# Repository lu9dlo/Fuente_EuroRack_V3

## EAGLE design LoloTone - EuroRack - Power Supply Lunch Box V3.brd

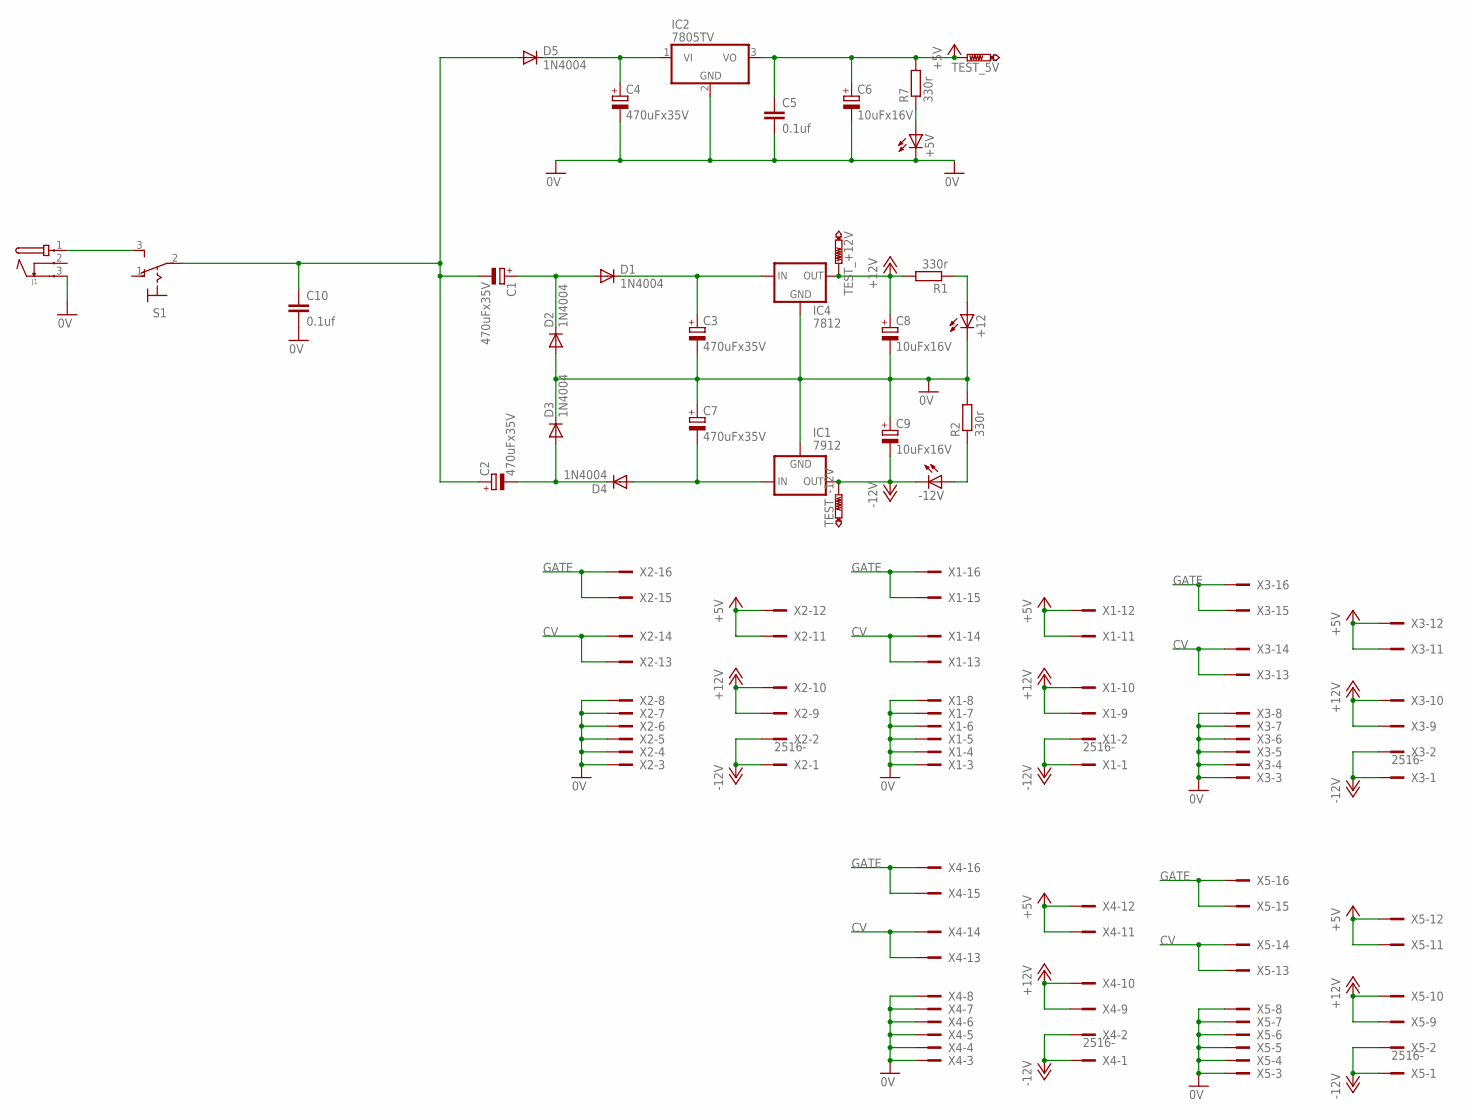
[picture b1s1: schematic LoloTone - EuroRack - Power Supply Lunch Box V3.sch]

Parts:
+5V, +12: LED5MM
-12V: LED5MM
C1, C2, C3, C4, C7: 470uFx35V; E5-10,5
C5: 0.1uf; C025-025X050
C6, C8, C9: 10uFx16V; E2,5-6E
C10: 0.1uf; C075-032X103
D1, D2, D3, D4, D5: 1N4004; DO41-10
IC1: 7912; 79XXS
IC2: 7805TV; TO220V
IC4: 7812; 78XXS
J1: JACK-PMS
R1, R2, R7: 330r; 0207/10
S1: 320-916
TEST_5V: PTR1PAD1-13Y; P1-13Y
TEST_+12V: PTR1PAD1-13Y; P1-13Y
TEST_-12V: PTR1PAD1-13Y; P1-13Y
X1, X2, X3, X4, X5: 2516-; PAK100/2500-16

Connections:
0V: +5V.K (C), +12.K (C), C3.-, C4.-, C5.2, C6.-, C7.+, C8.-, C9.+, C10.2, D2.A, D3.C, IC1.GND, IC2.2 (GND), IC4.GND, J1.3, R2.2, X1.3, X1.4, X1.5, X1.6, X1.7, X1.8, X2.3, X2.4, X2.5, X2.6, X2.7, X2.8, X3.3, X3.4, X3.5, X3.6, X3.7, X3.8, X4.3, X4.4, X4.5, X4.6, X4.7, X4.8, X5.3, X5.4, X5.5, X5.6, X5.7, X5.8
+5V: C5.1, C6.+, IC2.3 (VO), R7.2, TEST_5V.TP, X1.11, X1.12, X2.11, X2.12, X3.11, X3.12, X4.11, X4.12, X5.11, X5.12
+12V: C8.+, IC4.OUT, R1.2, TEST_+12V.TP, X1.9, X1.10, X2.9, X2.10, X3.9, X3.10, X4.9, X4.10, X5.9, X5.10
-12V: -12V.K (C), C9.-, IC1.OUT, TEST_-12V.TP, X1.1, X1.2, X2.1, X2.2, X3.1, X3.2, X4.1, X4.2, X5.1, X5.2
CV: X1.13, X1.14, X2.13, X2.14, X3.13, X3.14, X4.13, X4.14, X5.13, X5.14
GATE: X1.15, X1.16, X2.15, X2.16, X3.15, X3.16, X4.15, X4.16, X5.15, X5.16
unnamed: C1.+, D1.A, D2.C
unnamed: C1.-, C2.+, C10.1, D5.A, S1.2
unnamed: +5V.A, R7.1
unnamed: C2.-, D3.A, D4.C
unnamed: J1.1, S1.3 (S)
unnamed: C7.-, D4.A, IC1.IN
unnamed: C3.+, D1.C, IC4.IN
unnamed: +12.A, R1.1
unnamed: -12V.A, R2.1
unnamed: C4.+, D5.C, IC2.1 (VI)

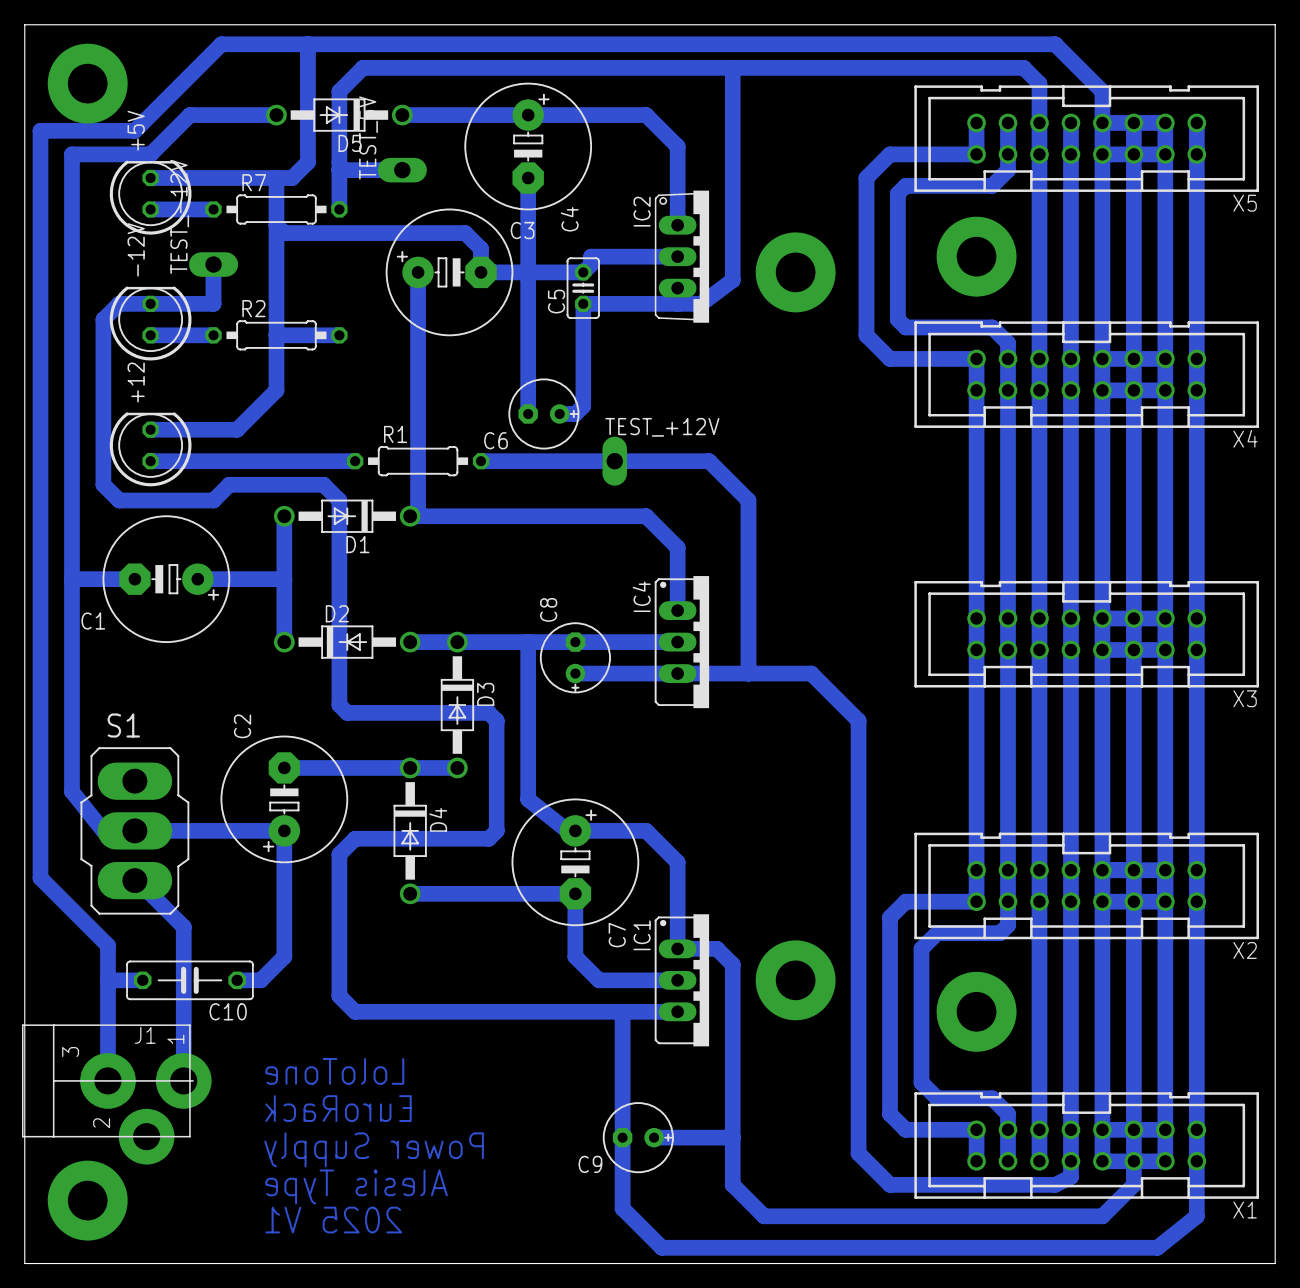
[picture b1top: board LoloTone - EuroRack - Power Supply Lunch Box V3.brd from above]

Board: 2 copper layers, 100.9 x 100.0 mm, 34 parts (0 on the bottom side), 16 nets.
